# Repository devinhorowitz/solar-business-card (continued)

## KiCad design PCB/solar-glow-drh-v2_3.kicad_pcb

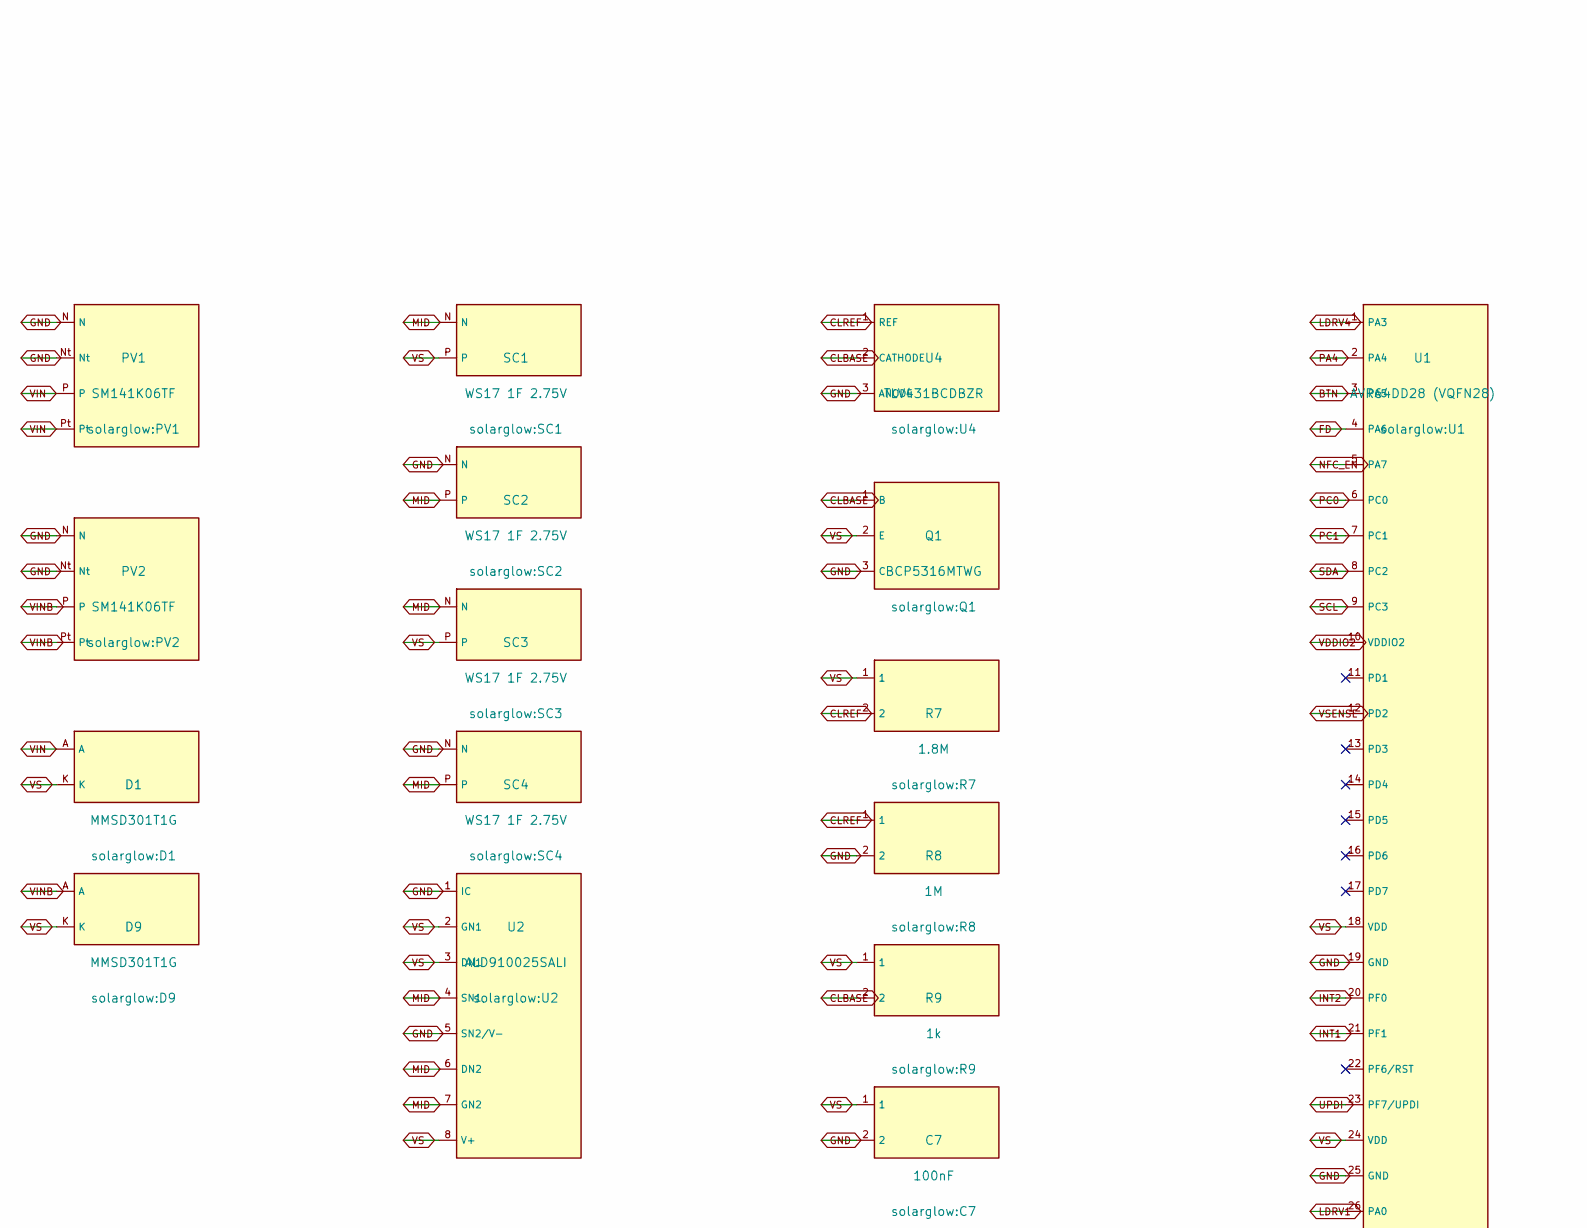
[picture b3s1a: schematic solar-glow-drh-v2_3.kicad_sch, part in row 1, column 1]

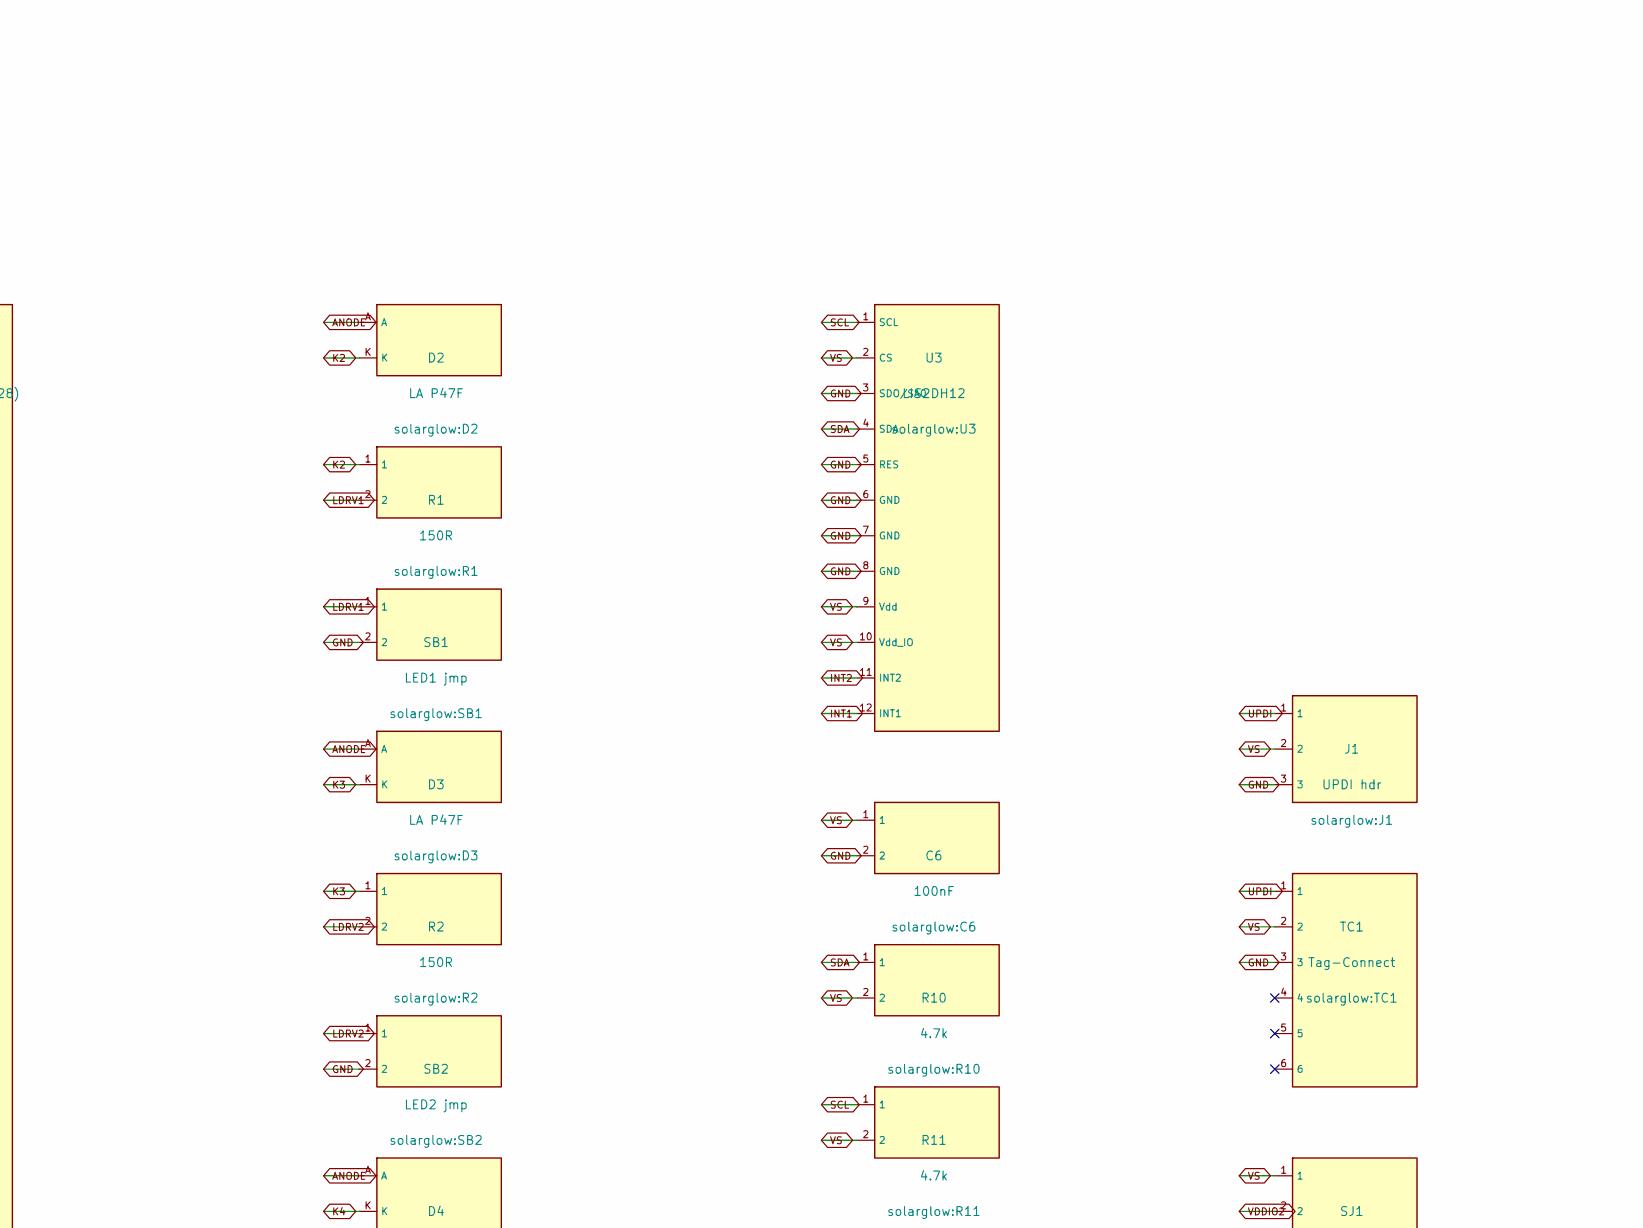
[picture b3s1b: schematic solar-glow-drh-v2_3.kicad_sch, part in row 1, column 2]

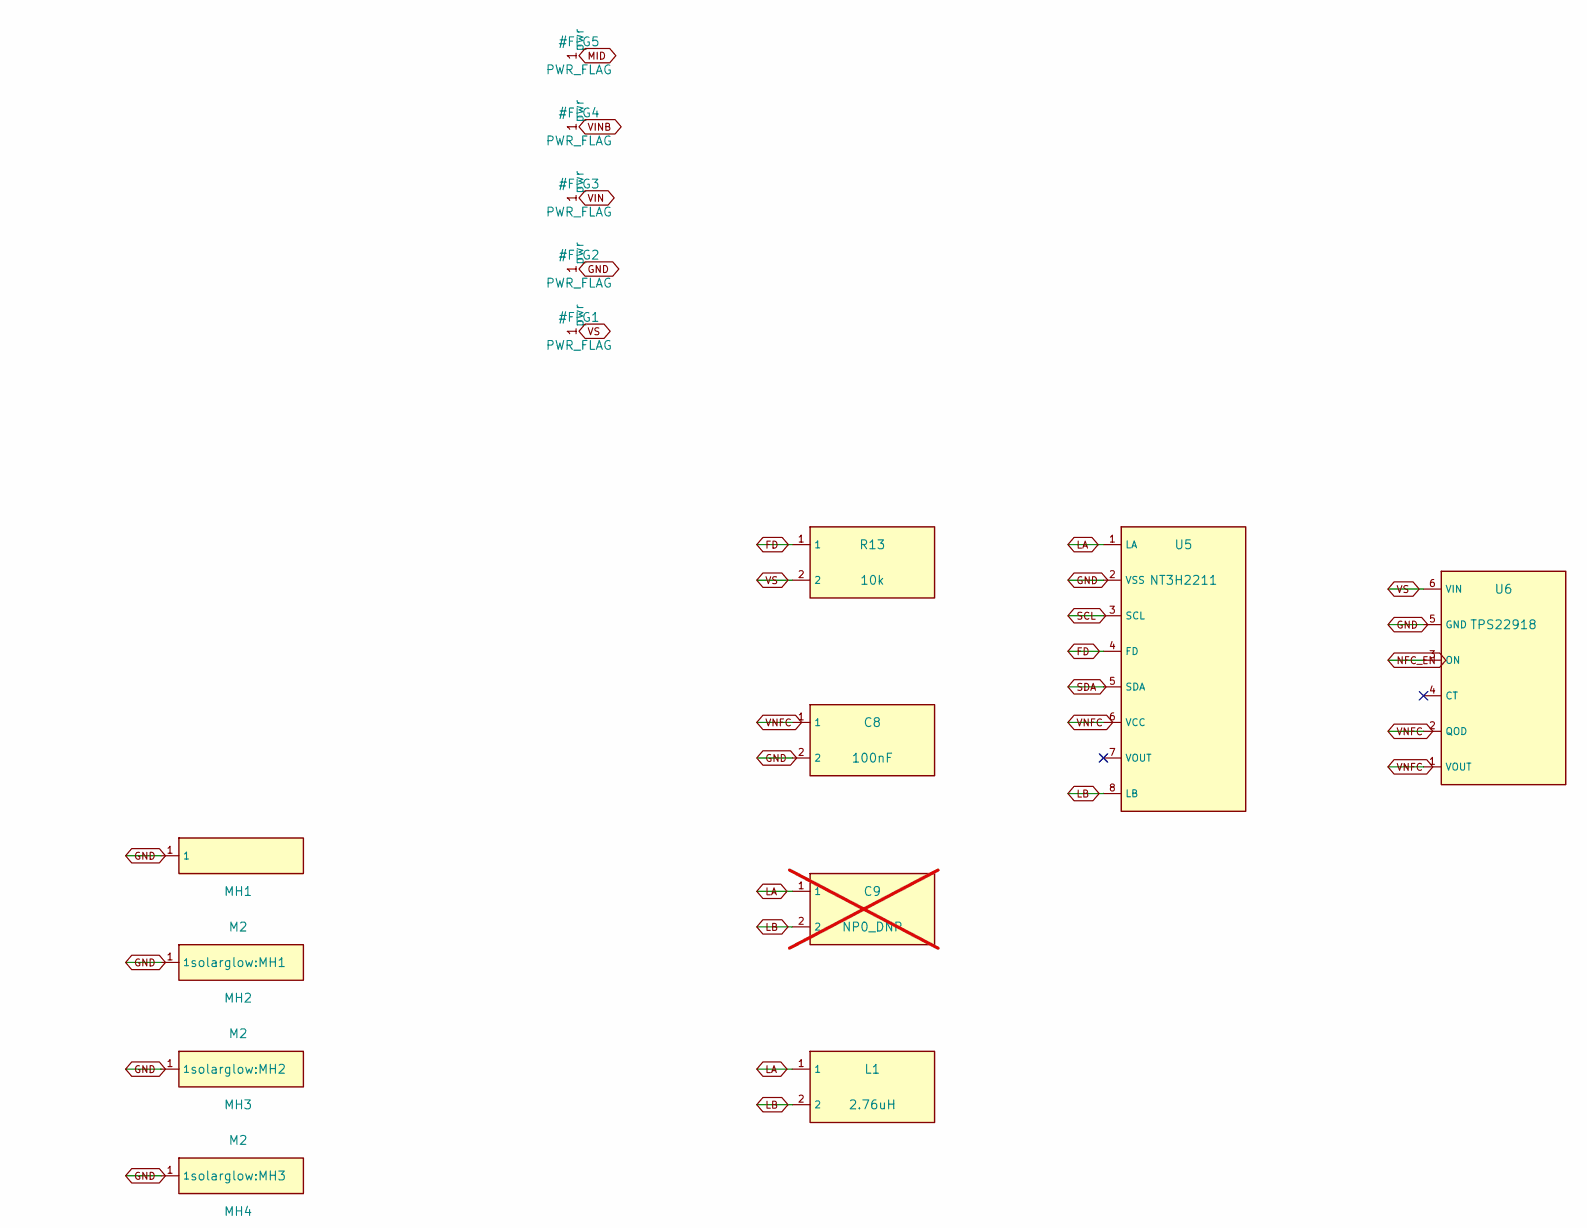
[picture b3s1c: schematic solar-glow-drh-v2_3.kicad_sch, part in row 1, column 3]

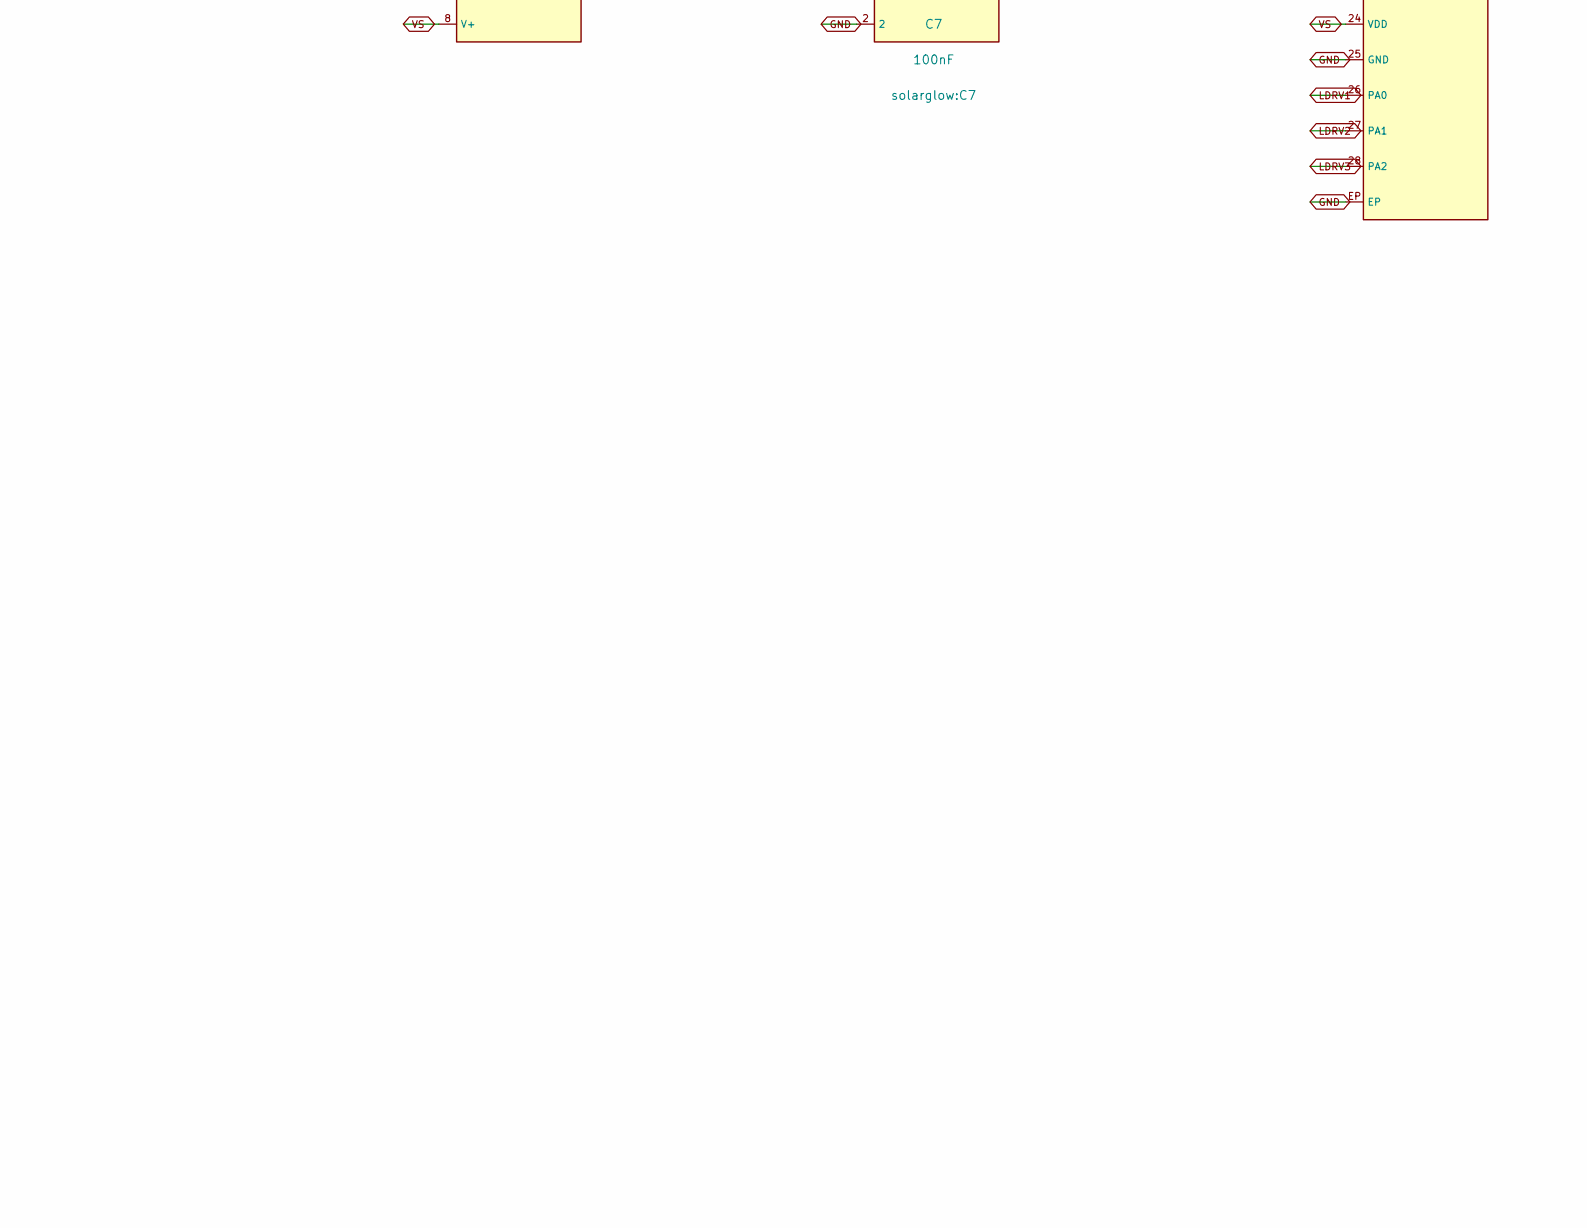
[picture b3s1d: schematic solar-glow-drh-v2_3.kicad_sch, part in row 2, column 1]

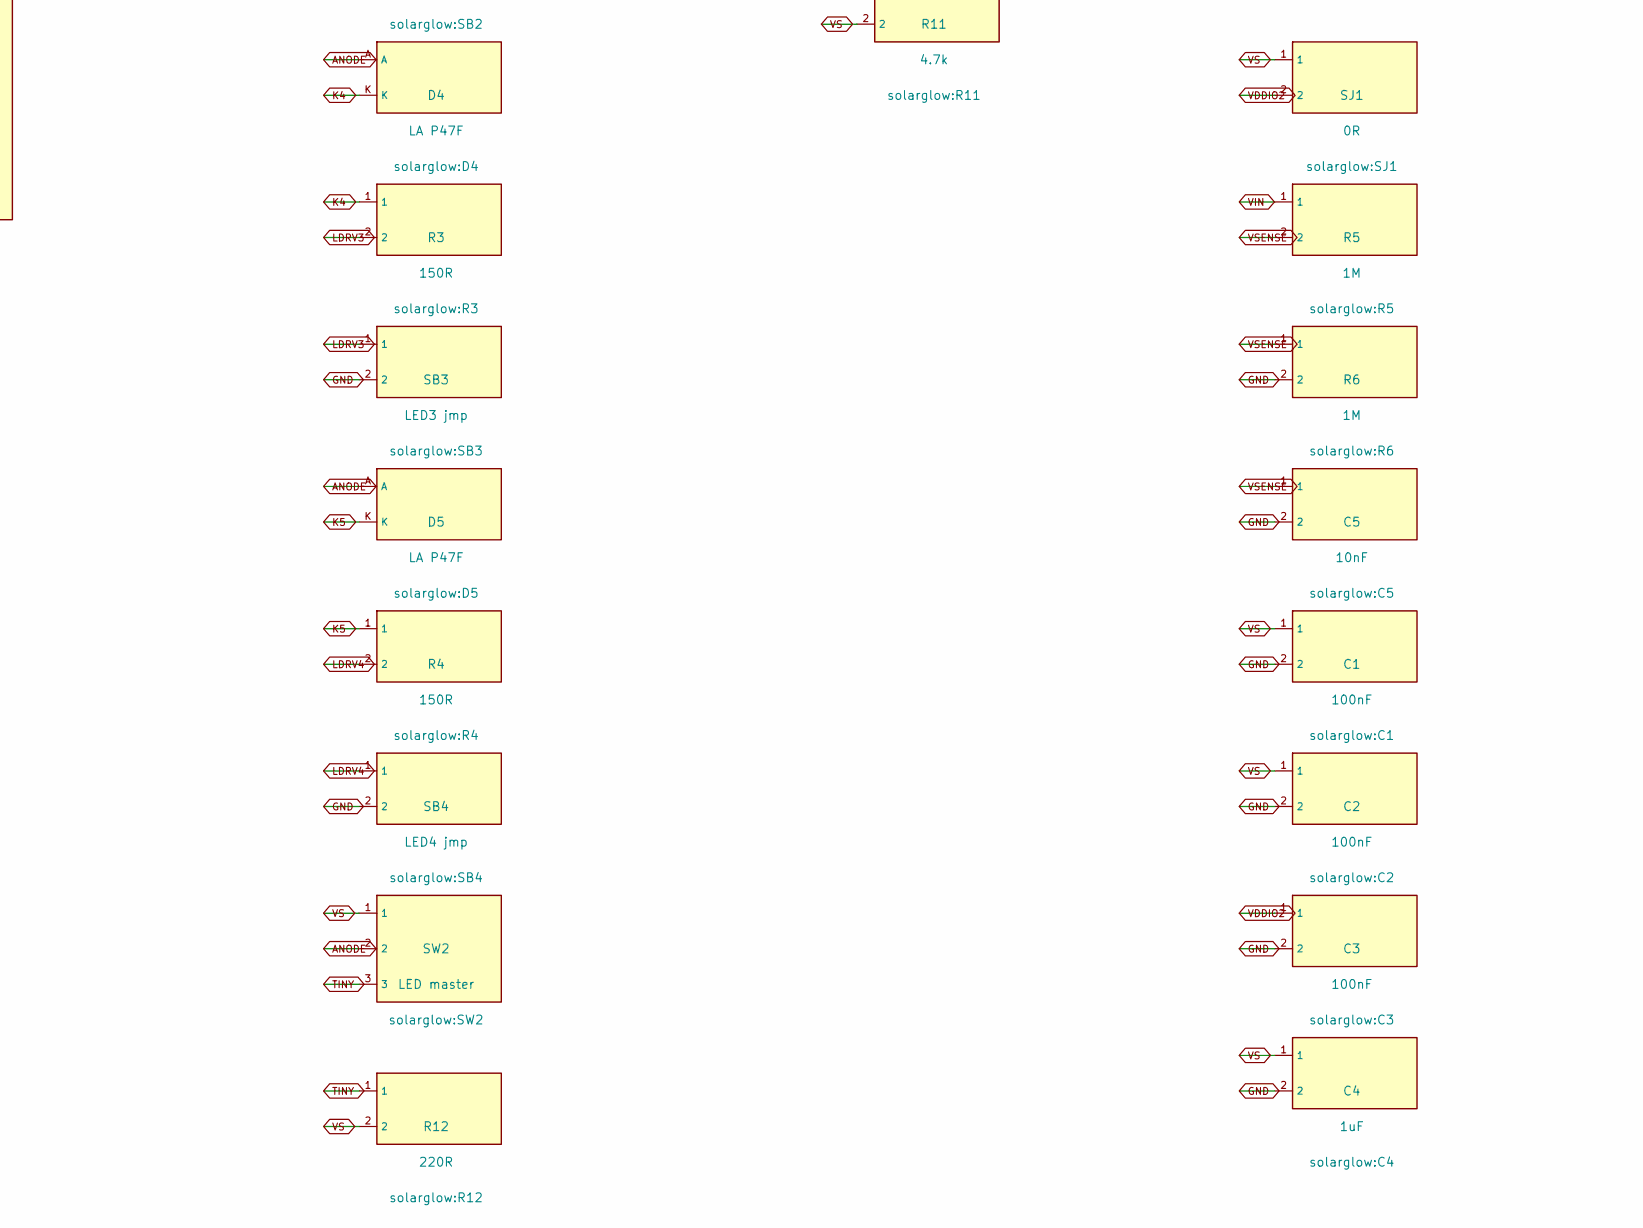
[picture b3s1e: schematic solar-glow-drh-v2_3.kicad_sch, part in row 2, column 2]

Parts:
C1: 100nF; C1
C2: 100nF; C2
C3: 100nF; C3
C4: 1uF; C4
C5: 10nF; C5
C6: 100nF; C6
C7: 100nF; C7
C8: 100nF; C8
C9: NP0_DNP; C9; not fitted
D1: MMSD301T1G; D1
D2: LA P47F; D2
D3: LA P47F; D3
D4: LA P47F; D4
D5: LA P47F; D5
D9: MMSD301T1G; D9
J1: UPDI hdr; J1
L1: 2.76uH
MH1: M2; MH1
MH2: M2; MH2
MH3: M2; MH3
MH4: M2; MH4
PV1: SM141K06TF; PV1
PV2: SM141K06TF; PV2
Q1: BCP5316MTWG; Q1
R1: 150R; R1
R2: 150R; R2
R3: 150R; R3
R4: 150R; R4
R5: 1M; R5
R6: 1M; R6
R7: 1.8M; R7
R8: 1M; R8
R9: 1k; R9
R10: 4.7k; R10
R11: 4.7k; R11
R12: 220R; R12
R13: 10k; R13
SB1: LED1 jmp; SB1
SB2: LED2 jmp; SB2
SB3: LED3 jmp; SB3
SB4: LED4 jmp; SB4
SC1: WS17 1F 2.75V; SC1
SC2: WS17 1F 2.75V; SC2
SC3: WS17 1F 2.75V; SC3
SC4: WS17 1F 2.75V; SC4
SJ1: 0R; SJ1
SW2: LED master; SW2
TC1: Tag-Connect; TC1
U1: AVR64DD28 (VQFN28); U1
U2: ALD910025SALI; U2
U3: LIS2DH12; U3
U4: TLV431BCDBZR; U4
U5: NT3H2211; U5
U6: TPS22918; SOT-23-6

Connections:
ANODE: D2.A, D3.A, D4.A, D5.A, SW2.2
BTN: U1.3 (PA5)
CLBASE: Q1.1 (B), R9.2, U4.2 (CATHODE)
CLREF: R7.2, R8.1, U4.1 (REF)
FD: R13.1, U1.4 (PA6), U5.4 (FD)
GND: C1.2, C2.2, C3.2, C4.2, C5.2, C6.2, C7.2, C8.2, J1.3, MH1.1 (1_1), MH2.1 (1_1), MH3.1 (1_1), MH4.1 (1_1), PV1.N, PV1.Nt, PV2.N, PV2.Nt, Q1.3 (C), R6.2, R8.2, SB1.2, SB2.2, SB3.2, SB4.2, SC2.N, SC4.N, TC1.3, U1.19 (GND), U1.25 (GND), U1.EP, U2.1 (IC), U2.5 (SN2/V-), U3.3 (SDO/SA0), U3.5 (RES), U3.6 (GND), U3.7 (GND), U3.8 (GND), U4.3 (ANODE), U5.2 (VSS), U6.5 (GND)
INT1: U1.21 (PF1), U3.12 (INT1)
INT2: U1.20 (PF0), U3.11 (INT2)
K2: D2.K, R1.1
K3: D3.K, R2.1
K4: D4.K, R3.1
K5: D5.K, R4.1
LA: C9.1, L1.1, U5.1 (LA)
LB: C9.2, L1.2, U5.8 (LB)
LDRV1: R1.2, SB1.1, U1.26 (PA0)
LDRV2: R2.2, SB2.1, U1.27 (PA1)
LDRV3: R3.2, SB3.1, U1.28 (PA2)
LDRV4: R4.2, SB4.1, U1.1 (PA3)
MID: SC1.N, SC2.P, SC3.N, SC4.P, U2.4 (SN1), U2.6 (DN2), U2.7 (GN2)
NFC_EN: U1.5 (PA7), U6.3 (ON)
PA4: U1.2 (PA4)
PC0: U1.6 (PC0)
PC1: U1.7 (PC1)
SCL: R11.1, U1.9 (PC3), U3.1 (SCL), U5.3 (SCL)
SDA: R10.1, U1.8 (PC2), U3.4 (SDA), U5.5 (SDA)
TINY: R12.1, SW2.3
UPDI: J1.1, TC1.1, U1.23 (PF7/UPDI)
VDDIO2: C3.1, SJ1.2, U1.10 (VDDIO2)
VIN: D1.A, PV1.P, PV1.Pt, R5.1
VINB: D9.A, PV2.P, PV2.Pt
VNFC: C8.1, U5.6 (VCC), U6.1 (VOUT), U6.2 (QOD)
VS: C1.1, C2.1, C4.1, C6.1, C7.1, D1.K, D9.K, J1.2, Q1.2 (E), R7.1, R9.1, R10.2, R11.2, R12.2, R13.2, SC1.P, SC3.P, SJ1.1, SW2.1, TC1.2, U1.18 (VDD), U1.24 (VDD), U2.2 (GN1), U2.3 (DN1), U2.8 (V+), U3.2 (CS), U3.9 (Vdd), U3.10 (Vdd_IO), U6.6 (VIN)
VSENSE: C5.1, R5.2, R6.1, U1.12 (PD2)

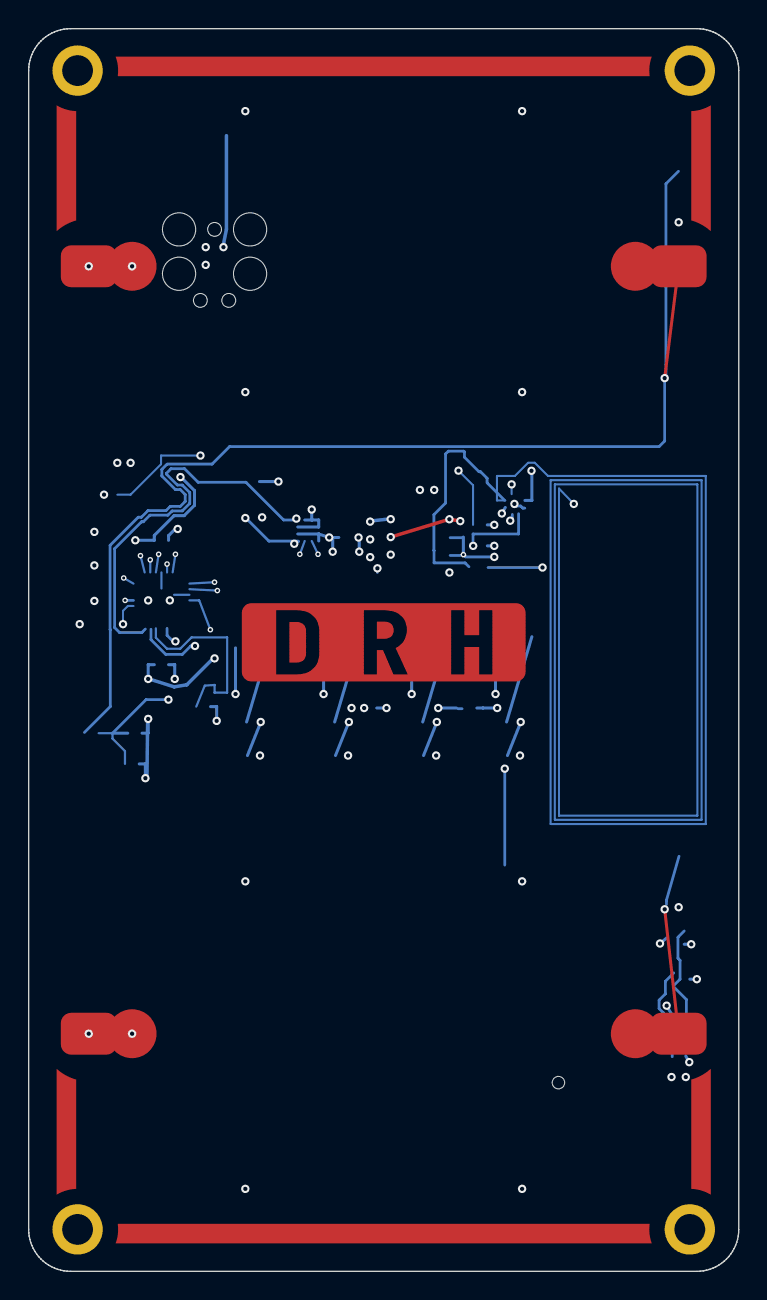
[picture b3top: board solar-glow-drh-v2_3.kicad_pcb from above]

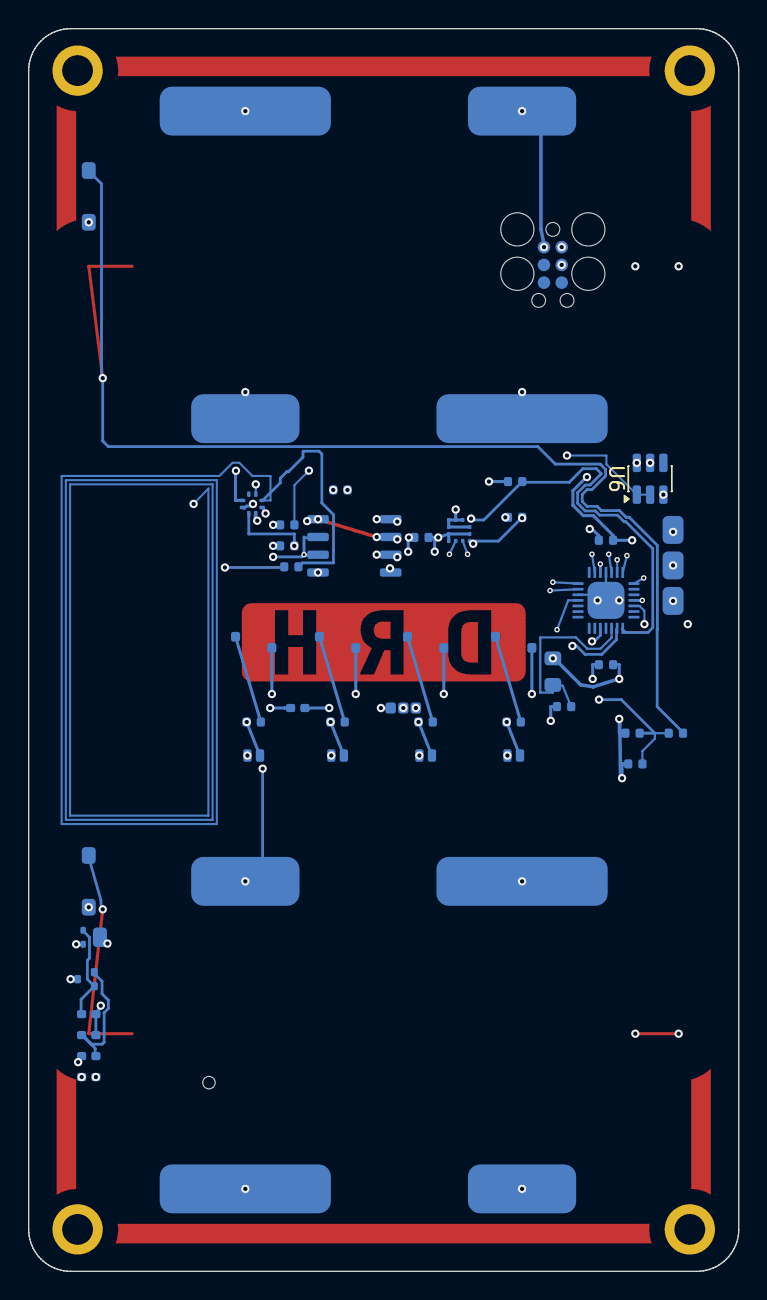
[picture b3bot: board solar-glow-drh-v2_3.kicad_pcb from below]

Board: 4 copper layers, 50.8 x 88.9 mm, 53 parts (47 on the bottom side), 29 nets.

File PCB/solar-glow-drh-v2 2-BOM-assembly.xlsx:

Ref(s) | Qty | Function | Value | Package / Footprint | Mfr | MPN (orderable) | ≈$/ea* | Ext $ | Status | Sourcing note / flag | Datasheet (repo) | DigiKey P/N
U1 | 1 | MCU — 8-bit AVR; PWM, I²C, charge/sleep logic | AVR64DD28, 64 KB, 24 MHz | VQFN-28 (4×4×1.0 mm, w/ EP) | Microchip | AVR64DD28-I/STX | 1.52 | 1.52 | LOCKED | VQFN land has an exposed pad → EP to GND. /STX confirmed = VQFN-28 (4×4). | AVR64DD32-28-Complete-DataSheet-DS40002315.pdf | (by MPN)
D1, D9 | 2 | Per-panel blocking Schottky (VIN/VINB→VS); isolates cells + caps in the dark | Schottky, Vf≈0.3–0.6 V | SOD-123 | onsemi | MMSD301T1G | 0.125 | 0.25 | LOCKED | Low-Vf for the ~4 V solar; one per panel so a half-shadow can't back-feed. | MMSD301T1-D.PDF | MMSD301T1GOSCT-ND
U2 | 1 | Supercap balancer — dual SAB MOSFET across the MID node (auto leakage balance; 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 | Dual SAB, ~0.3 nA–1 mA | SOIC-8 | Advanced Linear Devices | ALD910025SALI | 7.68 | 7.68 | LOCKED | ALD810025-2.pdf is the combined 810025/910025 datasheet — it covers this dual. 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 | ALD810025-2.pdf | ALD910025SALI-ND
D2–D5 | 4 | Glow LEDs — reverse-mount; emit through the bare-FR4 'DRH' window | Amber 617 nm, Vf≈2.25 V | PointLED 2-SMD flat-lead, ~3.4×1.25 mm | ams OSRAM | LA P47F-V2BB-24-3B5A-30-R18-Z | 0.273 | 1.092 | LOCKED | Reverse-mount; light path runs through the all-layer keepout window. | LA P47F_EN-2.pdf | 475-LAP47F-V2BB-24-3B5A-30-R18-ZCT-ND
R1–R4 | 4 | LED ballast — one per LED; sets per-LED current (low-side PWM) | 150 Ω, ±1% | 0402 | Yageo | RC0402FR-07150RL | 0.1 | 0.4 | SIZED | Package corrected to 0402 to match the placed land (BOM previously listed 1206;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 | — | (by MPN)
R12 | 1 | TINY-mode ballast — dims all LEDs via SW2 'TINY' for long-runtime glow | 220 Ω, ±1% | 0805 | Yageo | RC0805FR-07220RL | 0.1 | 0.1 | LOCKED | Sets the SW2 TINY dim level; tunable. | — | (by MPN)
R5, R6 | 2 | VSENSE divider — taps the solar input (VIN÷2) into PD2 | 1 MΩ, ±1% | 0805 | Yageo | RC0805FR-071ML | 0.1 | 0.2 | LOCKED | R5=R6 → VSENSE = VIN/2 (tracks light, ~0 V dark). Feeds ADC + the AC0 wake-on-l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 | — | (by MPN)
C5 | 1 | VSENSE filter cap | 10 nF, X7R, 50 V | 0805 | Samsung | CL21B103KBANNNC | 0.05 | 0.05 | LOCKED | RC filter on the VSENSE node. | (Samsung CL21 family) | (by MPN)
U3 | 1 | 3-axis accelerometer — tap/double-tap wake; INT1/INT2 → PF1/PF0 | I²C 0x18, ±2–16 g | LGA-12 (2×2×1.0 mm) | STMicroelectronics | LIS2DH12TR | 2.5 | 2.5 | LOCKED | CS→VS (I²C mode), SDO/SA0→GND (addr 0x18). SCL=PC3, SDA=PC2. | en.DM00091513.pdf | (by MPN)
R10, R11 | 2 | I²C pull-ups (TWI0 host on PC2/PC3) → VS | 4.7 kΩ, ±1% | 0805 | Yageo | RC0805FR-074K7L | 0.1 | 0.2 | LOCKED | Required — open-drain TWI bus. Firmware must set TWIROUTEA = ALT2. | — | (by MPN)
U4 | 1 | Rail-clamp reference — TLV431B (±0.5%); sets the VS trip | Vref 1.24 V, ±0.5% | SOT-23 (DBZ) | Texas Instruments | TLV431BCDBZR | 0.4 | 0.4 | LOCKED | B grade (tighter) for a predictable clamp. tlv431a-3.pdf is TI's combined A/B d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 | tlv431a-3.pdf | (by MPN)
Q1 | 1 | Rail-clamp pass PNP — shunts VS→GND when U4 trips | PNP (BCP53 family) | SOT / WDFN | onsemi | BCP5316MTWG | 0.45 | 0.45 | LOCKED | Emitter=VS, collector=GND, base=CLBASE. | BCP53M-D.PDF | (by MPN)
R7 | 1 | Clamp divider top — sets VS trip with R8 | 1.8 MΩ, ±1% | 0805 | Yageo | RC0805FR-071M8L | 0.1 | 0.1 | LOCKED | Trip = 1.24×(1+R7/R8) = 3.47 V. | — | (by MPN)
R8 | 1 | Clamp divider bottom | 1 MΩ, ±1% | 0805 | Yageo | RC0805FR-071ML | 0.1 | 0.1 | LOCKED | Divider midpoint (CLREF) → TLV431 ref. | — | (by MPN)
R9 | 1 | Clamp base pull-up / cathode path | 1 kΩ, ±1% | 0805 | Yageo | RC0805FR-071KL | 0.1 | 0.1 | LOCKED | VS→CLBASE; holds Q1 off until U4 conducts. | — | (by MPN)
C1 | 1 | MCU decoupling (VDD) | 100 nF, X7R, 25 V | 0805 | Samsung | CL21B104KBCWPNC | 0.09 | 0.09 | LOCKED |  | (Samsung CL21 family) | 1276-6557-1-ND
C2, C3 | 2 | Decoupling — VDDIO2 / MCU | 100 nF, X7R, 25 V | 0805 | Samsung | CL21B104KBCWPNC | 0.09 | 0.18 | LOCKED |  | (Samsung CL21 family) | 1276-6557-1-ND
C4 | 1 | VS-rail bulk decoupling | 1 µF, X7S, 10 V | 0805 | Samsung | CL21A105KBCLNNC | 0.04 | 0.04 | LOCKED |  | CL21A105KBCLNNC Spec.pdf | (by MPN)
C6 | 1 | Accelerometer decoupling | 100 nF, X7R, 25 V | 0805 | Samsung | CL21B104KBCWPNC | 0.09 | 0.09 | LOCKED |  | (Samsung CL21 family) | 1276-6557-1-ND
C7 | 1 | Clamp local decoupling | 100 nF, X7R, 25 V | 0805 | Samsung | CL21B104KBCWPNC | 0.09 | 0.09 | LOCKED |  | (Samsung CL21 family) | 1276-6557-1-ND
SJ1 | 1 | VDDIO2 tie — bonds VDDIO2 to VS (MVIO unused) | 0 Ω jumper | 0805 | Yageo | RC0805JR-070RL | 0.05 | 0.05 | LOCKED |  | — | (by MPN)
U5 | 1 | NFC tag — NTAG I²C plus 2K; phone reads/writes EEPROM, FD signals field to MCU | NTAG I²C plus, 2 KB, I²C 0x55 | XQFN8 (SOT902-3, 1.6×1.6×0.5 mm) | NXP | NT3H2211W0FHKH | 0.75 | 0.75 | LOCKED | v2.2 NFC addition. XQFN8 = SOT902-3 (datasheet Table 1). I²C 0x55 (no clash w/ 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 | NT3H2111_2211.pdf | (by MPN)
C8 | 1 | NFC tag (U5) VCC decoupling | 100 nF, X7R, 25 V | 0805 | Samsung | CL21B104KBCWPNC | 0.09 | 0.09 | LOCKED | v2.2 NFC addition. Same part as C1/C2/C3/C6/C7. | (Samsung CL21 family) | 1276-6557-1-ND
R13 | 1 | NFC FD pull-up — open-drain FD (U5 pin 4) → PA6 | 10 kΩ, ±1% | 0805 | Yageo | RC0805FR-0710KL | 0.1 | 0.1 | LOCKED | v2.2 NFC addition. Pulls open-drain FD up to VS. | — | (by MPN)
Placed-parts subtotal (per board) |  |  |  |  |  |  |  | 16.622
NOTE: PCBWay turnkey BOM. Machine-placed parts ONLY (bottom side).
Hand-soldered by customer, NOT on this BOM: SC1-SC4 (supercaps), PV1-PV2 (solar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
Not placed: SW2, SB1-SB4 (bridges), TC1 (Tag-Connect), J1/JP1/JP2 (headers), MH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
